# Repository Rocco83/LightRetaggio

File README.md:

# LightRetaggio

KiCad project for the LightRetaggioSchema board (LightController breakout), migrated from the original Eagle design.

## Repository layout

- `kicad/` — the active KiCad project (KiCad 10.0)
  - `LightRetaggioSchema.kicad_pro` — project file, open this in KiCad
  - `LightRetaggioSchema.kicad_sch` — schematic
  - `LightRetaggioSchema.kicad_pcb` — PCB layout
  - `LightRetaggioSchema-eagle-import.kicad_sym` — symbol library generated by the Eagle import
  - `LightRetaggioSchema.pretty/` — footprint library extracted from the imported board, registered in `fp-lib-table`
  - `sym-lib-table`, `fp-lib-table` — project-local library tables (paths are relative, no extra setup needed)
- `LightRetaggioSchema.sch` / `.brd` / `.pro` — original Eagle source (kept for reference)
- `LightRetaggioSchema_2020-04-23.zip` — archived Eagle export
- `eagle.epf` — Eagle workspace file

## Requirements

- [KiCad 10.0](https://www.kicad.org/download/) or newer

## Setup / build instructions

1. Install KiCad 10.0+.
2. Clone this repository:
   ```
   git clone https://github.com/Rocco83/LightRetaggio.git
   cd LightRetaggio
   ```
3. Open `kicad/LightRetaggioSchema.kicad_pro` in KiCad. The symbol and footprint libraries are referenced with relative paths in `sym-lib-table` / `fp-lib-table`, so no library setup is required beyond opening the project.
4. To edit: open the schematic (Eeschema) or PCB (Pcbnew) from the KiCad project manager.
5. To regenerate manufacturing outputs:
   - Gerbers/drill: Pcbnew → File → Fabrication Outputs → Gerbers / Drill Files
   - BOM: Eeschema → Tools → Generate Bill of Materials
   - Pick-and-place: Pcbnew → File → Fabrication Outputs → Component Placement Files

## Notes on the migration

The board was imported from the original Eagle source (rev V1.2, 2021-04-19) using KiCad's combined Eagle project importer. The importer generates a symbol library but no footprint library, so the footprints embedded in the imported board were extracted into `kicad/LightRetaggioSchema.pretty/` and registered under the `LightRetaggioSchema` nickname.

Verified clean after migration:
- **DRC**: 0 unconnected items, 0 footprint errors (remaining violations are cosmetic silkscreen/text sizing rules KiCad enforces more strictly than Eagle did)
- **ERC**: remaining violations are expected (unused switch pins, NC optocoupler pins, and a VCC/GND dual-net-naming convention already approved in the original Eagle file)

The original Eagle files (`.sch`, `.brd`, `.pro`) are kept at the repository root for reference/history.

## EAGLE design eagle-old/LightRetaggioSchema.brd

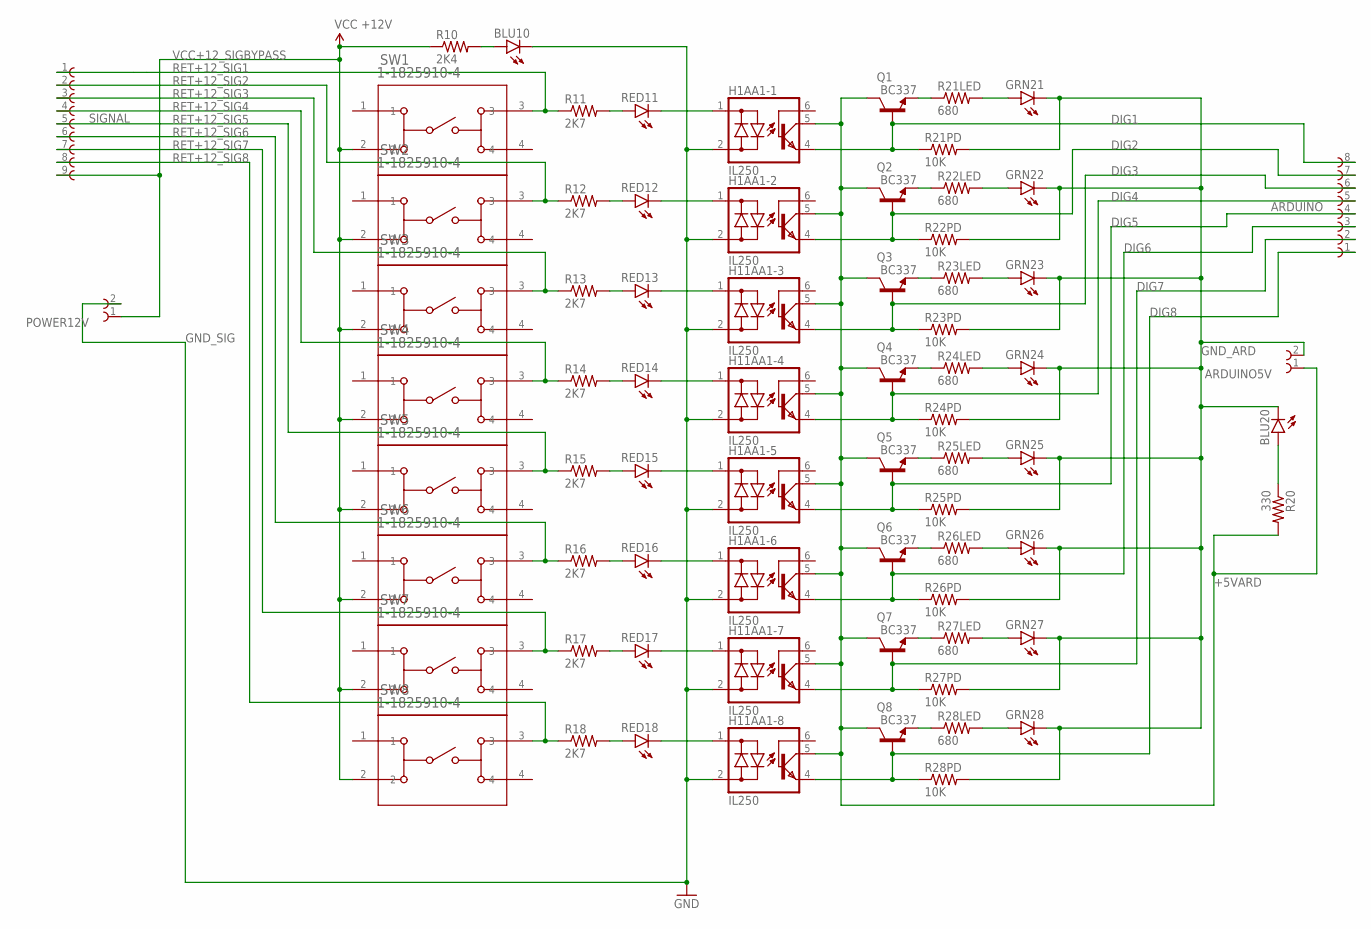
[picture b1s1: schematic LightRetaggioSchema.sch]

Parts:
ARDUINO: 691311500108
ARDUINO5V: 691311500102; MPN 691311500102
BLU10, BLU20: LED5MM; MPN FSM8JH
GRN21, GRN22, GRN23, GRN24, GRN25, GRN26, GRN27, GRN28: LED5MM; MPN FSM8JH
H1AA1-1, H1AA1-2, H1AA1-5, H1AA1-6, H11AA1-3, H11AA1-4, H11AA1-7, H11AA1-8: IL250; DIL06
POWER12V: 691311500102; MPN 691311500102
Q1, Q2, Q3, Q4, Q5, Q6, Q7, Q8: BC337; TO-92
R10: 2K4; AXIAL-0.4
R11, R12, R13, R14, R15, R16, R17, R18: 2K7; AXIAL-0.4
R20: 330; AXIAL-0.4
R21LED, R22LED, R23LED, R24LED, R25LED, R26LED, R27LED, R28LED: 680; AXIAL-0.4
R21PD, R22PD, R23PD, R24PD, R25PD, R26PD, R27PD, R28PD: 10K; AXIAL-0.4
RED11, RED12, RED13, RED14, RED15, RED16, RED17, RED18: LED5MM; MPN FSM8JH
SIGNAL: 691311500109
SW1, SW2, SW3, SW4, SW5, SW6, SW7, SW8: 1-1825910-4; SW4_1825910-D

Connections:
+5VARD: ARDUINO5V.1, H1AA1-1.5 (C), H1AA1-2.5 (C), H1AA1-5.5 (C), H1AA1-6.5 (C), H11AA1-3.5 (C), H11AA1-4.5 (C), H11AA1-7.5 (C), H11AA1-8.5 (C), Q1.1 (C), Q2.1 (C), Q3.1 (C), Q4.1 (C), Q5.1 (C), Q6.1 (C), Q7.1 (C), Q8.1 (C), R20.P$2 (2)
DIG1: ARDUINO.8, H1AA1-1.4 (E), Q1.2 (B), R21PD.P$1 (1)
DIG2: ARDUINO.7, H1AA1-2.4 (E), Q2.2 (B), R22PD.P$1 (1)
DIG3: ARDUINO.6, H11AA1-3.4 (E), Q3.2 (B), R23PD.P$1 (1)
DIG4: ARDUINO.5, H11AA1-4.4 (E), Q4.2 (B), R24PD.P$1 (1)
DIG5: ARDUINO.4, H1AA1-5.4 (E), Q5.2 (B), R25PD.P$1 (1)
DIG6: ARDUINO.3, H1AA1-6.4 (E), Q6.2 (B), R26PD.P$1 (1)
DIG7: ARDUINO.2, H11AA1-7.4 (E), Q7.2 (B), R27PD.P$1 (1)
DIG8: ARDUINO.1, H11AA1-8.4 (E), Q8.2 (B), R28PD.P$1 (1)
GND_ARD: ARDUINO5V.2, BLU20.K (C), GRN21.K (C), GRN22.K (C), GRN23.K (C), GRN24.K (C), GRN25.K (C), GRN26.K (C), GRN27.K (C), GRN28.K (C), R21PD.P$2 (2), R22PD.P$2 (2), R23PD.P$2 (2), R24PD.P$2 (2), R25PD.P$2 (2), R26PD.P$2 (2), R27PD.P$2 (2), R28PD.P$2 (2)
GND_SIG: BLU10.K (C), H1AA1-1.2 (AC2), H1AA1-2.2 (AC2), H1AA1-5.2 (AC2), H1AA1-6.2 (AC2), H11AA1-3.2 (AC2), H11AA1-4.2 (AC2), H11AA1-7.2 (AC2), H11AA1-8.2 (AC2), POWER12V.2
unnamed: BLU10.A, R10.P$2 (2)
unnamed: BLU20.A, R20.P$1 (1)
unnamed: H11AA1-8.1 (AC1), RED18.K (C)
unnamed: H11AA1-7.1 (AC1), RED17.K (C)
unnamed: H1AA1-6.1 (AC1), RED16.K (C)
unnamed: H1AA1-5.1 (AC1), RED15.K (C)
unnamed: Q1.3 (E), R21LED.P$1 (1)
unnamed: GRN21.A, R21LED.P$2 (2)
unnamed: H11AA1-4.1 (AC1), RED14.K (C)
unnamed: Q2.3 (E), R22LED.P$1 (1)
unnamed: GRN22.A, R22LED.P$2 (2)
unnamed: Q3.3 (E), R23LED.P$1 (1)
unnamed: GRN23.A, R23LED.P$2 (2)
unnamed: Q4.3 (E), R24LED.P$1 (1)
unnamed: GRN24.A, R24LED.P$2 (2)
unnamed: R13.P$2 (2), RED13.A
unnamed: H11AA1-3.1 (AC1), RED13.K (C)
unnamed: R14.P$2 (2), RED14.A
unnamed: R12.P$2 (2), RED12.A
unnamed: R11.P$2 (2), RED11.A
unnamed: R17.P$2 (2), RED17.A
unnamed: R18.P$2 (2), RED18.A
unnamed: R16.P$2 (2), RED16.A
unnamed: R15.P$2 (2), RED15.A
unnamed: Q5.3 (E), R25LED.P$1 (1)
unnamed: GRN25.A, R25LED.P$2 (2)
unnamed: Q6.3 (E), R26LED.P$1 (1)
unnamed: GRN26.A, R26LED.P$2 (2)
unnamed: Q7.3 (E), R27LED.P$1 (1)
unnamed: GRN27.A, R27LED.P$2 (2)
unnamed: Q8.3 (E), R28LED.P$1 (1)
unnamed: GRN28.A, R28LED.P$2 (2)
unnamed: H1AA1-2.1 (AC1), RED12.K (C)
unnamed: H1AA1-1.1 (AC1), RED11.K (C)
RET+12_SIG1: R11.P$1 (1), SIGNAL.1, SW1.3
RET+12_SIG2: R12.P$1 (1), SIGNAL.2, SW2.3
RET+12_SIG3: R13.P$1 (1), SIGNAL.3, SW3.3
RET+12_SIG4: R14.P$1 (1), SIGNAL.4, SW4.3
RET+12_SIG5: R15.P$1 (1), SIGNAL.5, SW5.3
RET+12_SIG6: R16.P$1 (1), SIGNAL.6, SW6.3
RET+12_SIG7: R17.P$1 (1), SIGNAL.7, SW7.3
RET+12_SIG8: R18.P$1 (1), SIGNAL.8, SW8.3
VCC+12_SIGBYPASS: POWER12V.1, R10.P$1 (1), SIGNAL.9, SW1.2, SW2.2, SW3.2, SW4.2, SW5.2, SW6.2, SW7.2, SW8.2

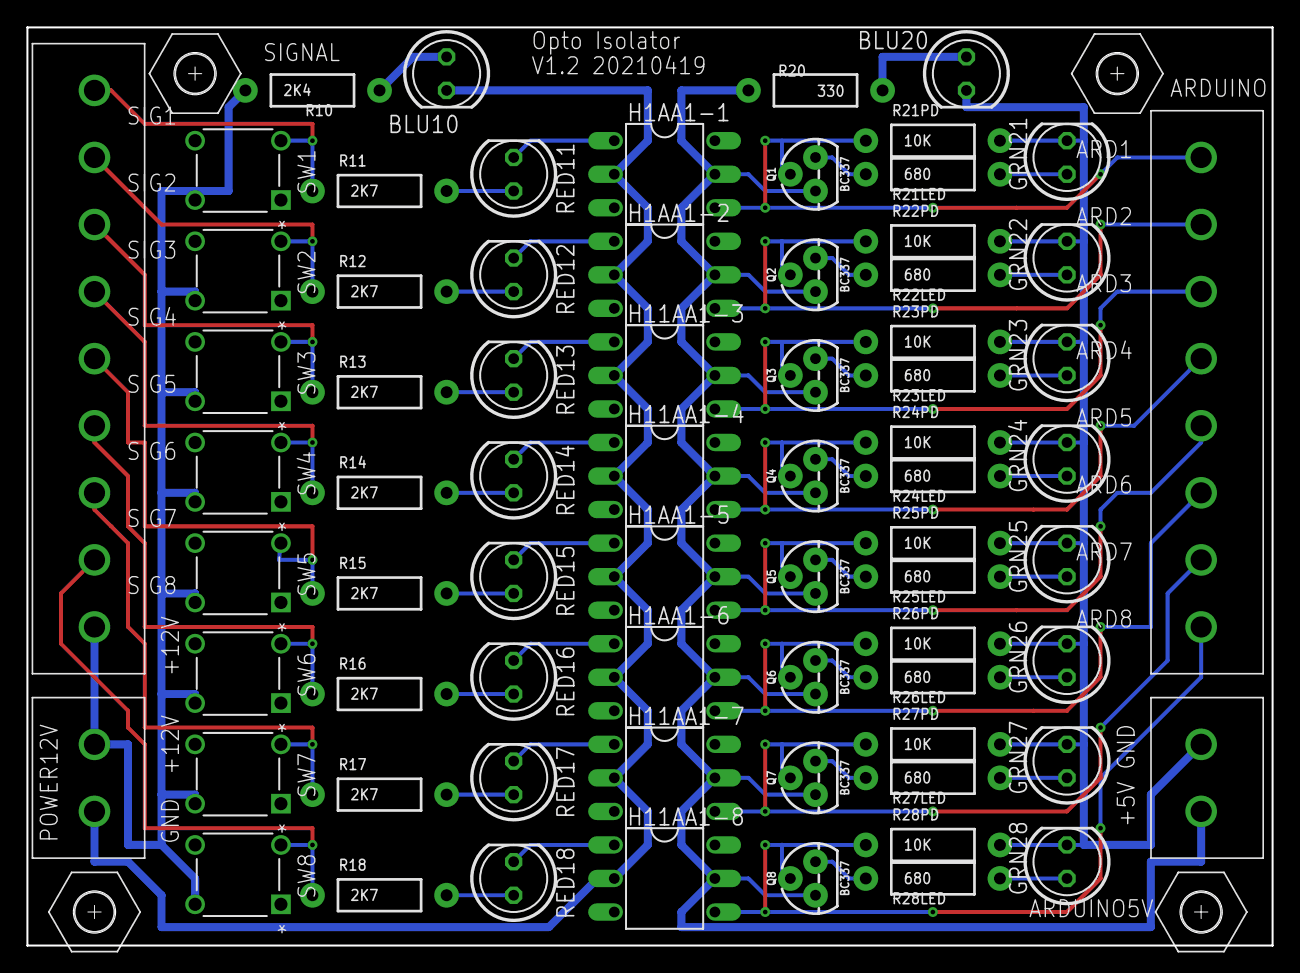
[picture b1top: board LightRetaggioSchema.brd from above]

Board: 2 copper layers, 94.3 x 69.5 mm, 76 parts (0 on the bottom side), 54 nets.

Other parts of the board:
U$1, U$2, U$3, U$5: M3.0_SW6.0

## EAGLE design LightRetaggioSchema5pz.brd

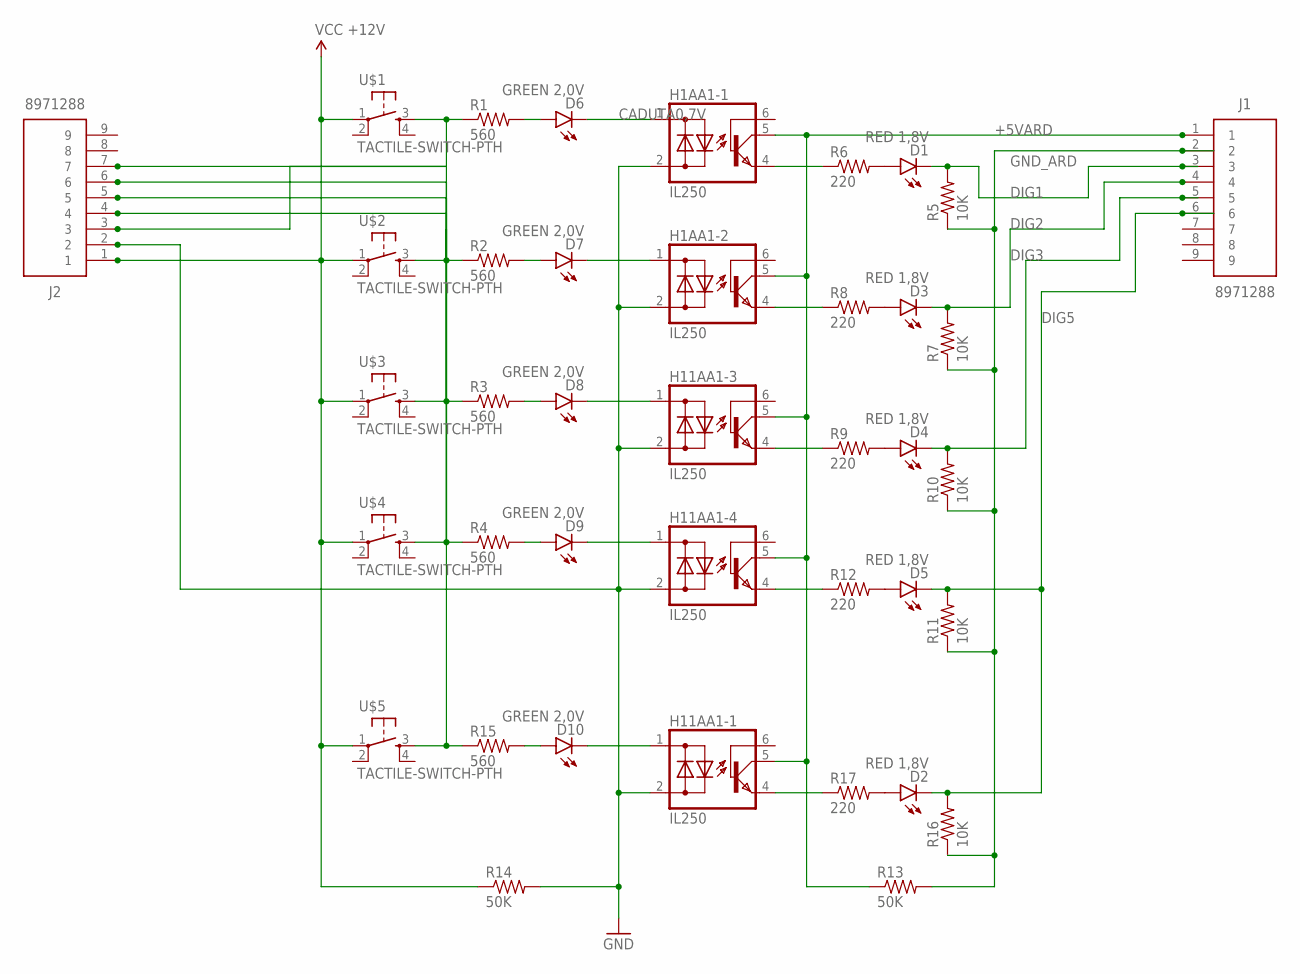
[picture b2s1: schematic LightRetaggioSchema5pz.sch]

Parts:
D1, D2, D3, D4, D5: RED 1,8V; LED-1206
D6, D7, D8, D9, D10: GREEN 2,0V; LED-1206
H1AA1-1, H1AA1-2, H11AA1-1, H11AA1-3, H11AA1-4: IL250; DIL06
J1, J2: 8971288; SHDR9W100P0X508_1X9_4690X1210X
R1, R2, R3, R4, R15: 560; AXIAL-0.4
R5, R7, R10, R11, R16: 10K; AXIAL-0.4
R6, R8, R9, R12, R17: 220; AXIAL-0.4
R13, R14: 50K; AXIAL-0.4
U$1, U$2, U$3, U$4, U$5: TACTILE-SWITCH-PTH; TAC-SWITCH-PTH

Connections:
+5VARD: H1AA1-1.5 (C), H1AA1-2.5 (C), H11AA1-1.5 (C), H11AA1-3.5 (C), H11AA1-4.5 (C), J1.1, R13.P$1 (1)
CADUTA0,7V: D6.C, H1AA1-1.1 (AC1)
DIG1: D1.C, J1.3, R5.P$2 (2)
DIG2: D3.C, J1.4, R7.P$2 (2)
DIG3: D4.C, J1.5, R10.P$2 (2)
DIG5: D2.C, D5.C, J1.6, R11.P$2 (2), R16.P$2 (2)
GND: H1AA1-1.2 (AC2), H1AA1-2.2 (AC2), H11AA1-1.2 (AC2), H11AA1-3.2 (AC2), H11AA1-4.2 (AC2), J2.2, R14.P$2 (2)
GND_ARD: J1.2, R5.P$1 (1), R7.P$1 (1), R10.P$1 (1), R11.P$1 (1), R13.P$2 (2), R16.P$1 (1)
unnamed: J2.4, J2.5, R3.P$1 (1), U$3.3
unnamed: R2.P$1 (1), U$2.3
unnamed: J2.6, R4.P$1 (1), U$4.3
unnamed: D9.C, H11AA1-4.1 (AC1)
unnamed: D8.C, H11AA1-3.1 (AC1)
unnamed: D7.C, H1AA1-2.1 (AC1)
unnamed: J2.3, R1.P$1 (1), U$1.3
unnamed: H1AA1-1.4 (E), R6.P$1 (1)
unnamed: D1.A, R6.P$2 (2)
unnamed: D4.A, R9.P$2 (2)
unnamed: D3.A, R8.P$2 (2)
unnamed: H1AA1-2.4 (E), R8.P$1 (1)
unnamed: D5.A, R12.P$2 (2)
unnamed: H11AA1-4.4 (E), R12.P$1 (1)
unnamed: D8.A, R3.P$2 (2)
unnamed: H11AA1-3.4 (E), R9.P$1 (1)
unnamed: D9.A, R4.P$2 (2)
unnamed: D7.A, R2.P$2 (2)
unnamed: D6.A, R1.P$2 (2)
unnamed: J2.7, R15.P$1 (1), U$5.3
unnamed: D10.C, H11AA1-1.1 (AC1)
unnamed: D2.A, R17.P$2 (2)
unnamed: H11AA1-1.4 (E), R17.P$1 (1)
unnamed: D10.A, R15.P$2 (2)
VCC: J2.1, R14.P$1 (1), U$1.1, U$2.1, U$3.1, U$4.1, U$5.1

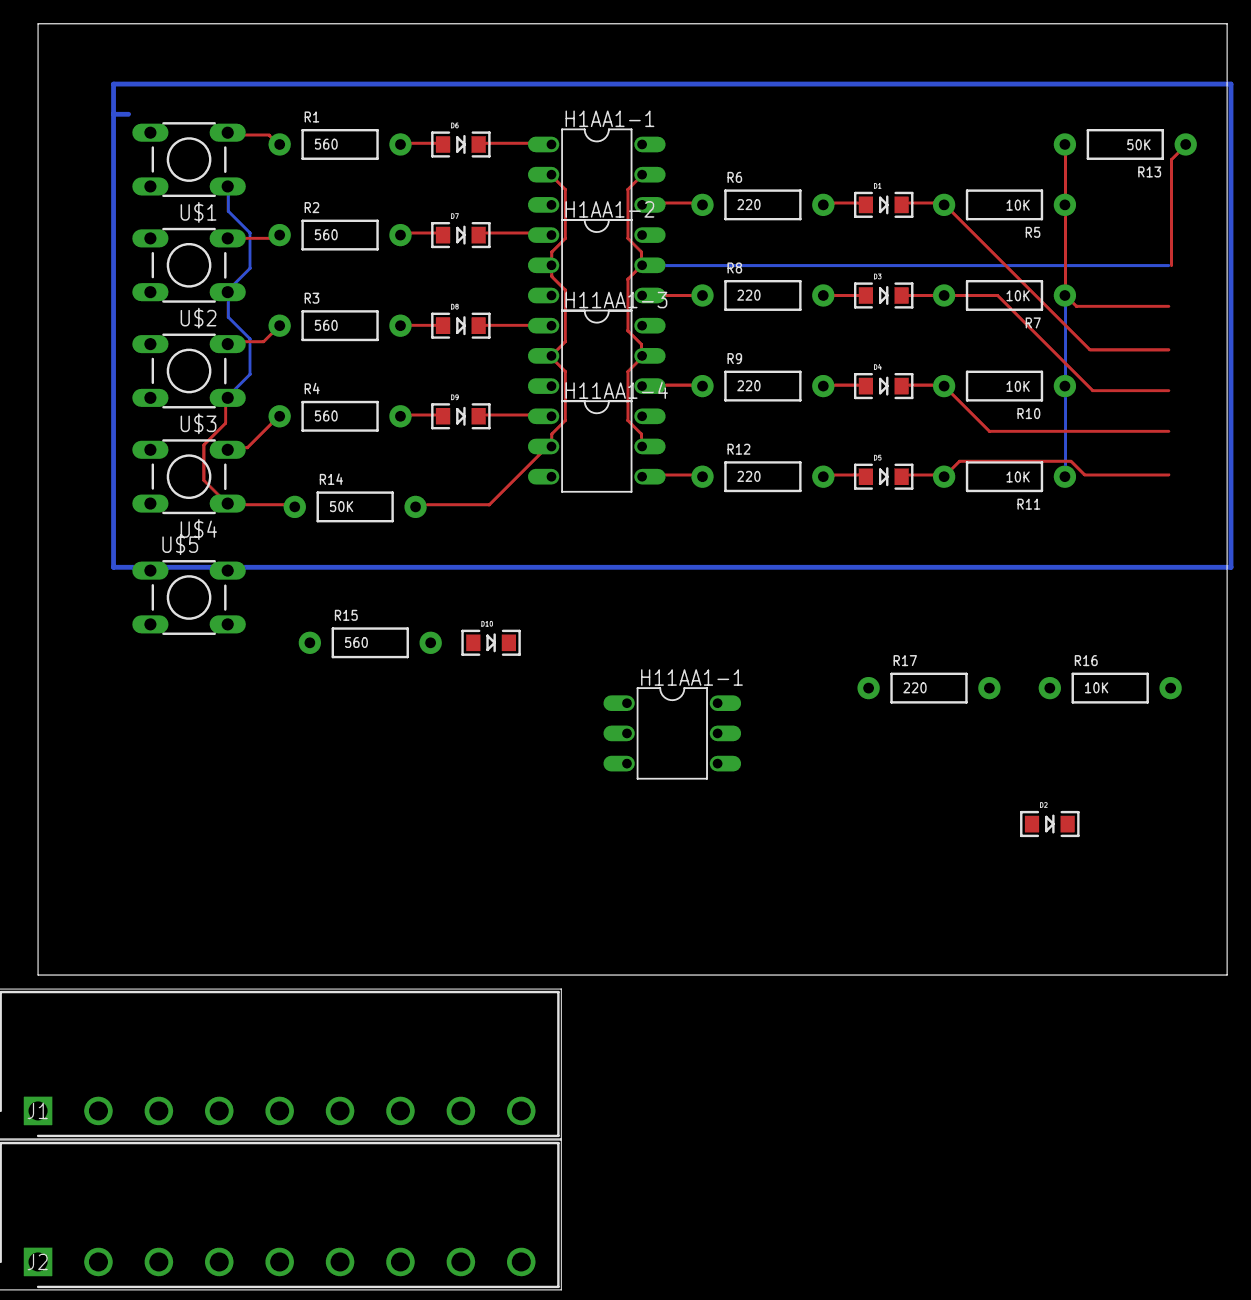
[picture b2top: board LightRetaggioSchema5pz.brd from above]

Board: 2 copper layers, 100.0 x 80.0 mm, 39 parts (0 on the bottom side), 33 nets.

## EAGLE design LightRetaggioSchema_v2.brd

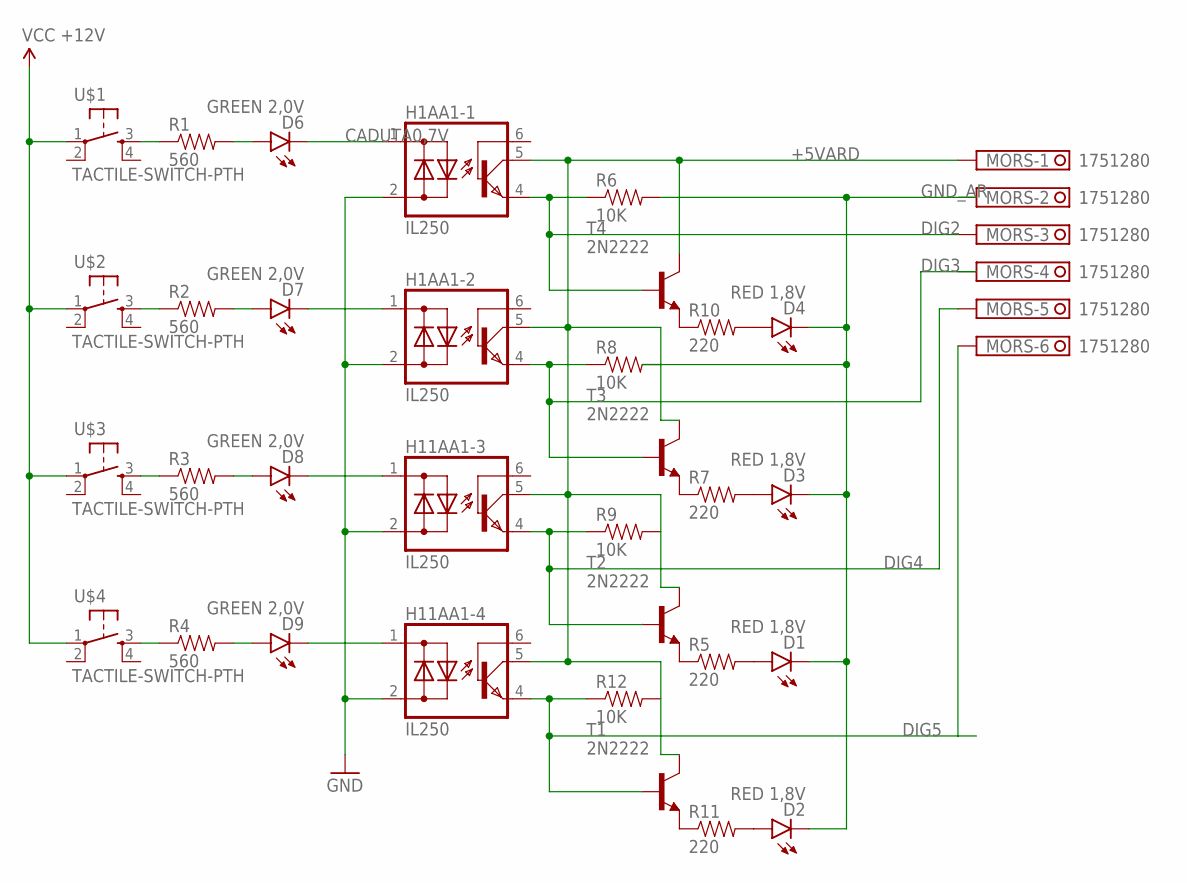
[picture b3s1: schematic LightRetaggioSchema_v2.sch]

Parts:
D1, D2, D3, D4: RED 1,8V; LED-1206
D6, D7, D8, D9: GREEN 2,0V; LED-1206
H1AA1-1, H1AA1-2, H11AA1-3, H11AA1-4: IL250; DIL06
MORS: 1751280
R1, R2, R3, R4: 560; AXIAL-0.4
R5, R7, R10, R11: 220; AXIAL-0.4
R6, R8, R9, R12: 10K; AXIAL-0.4
T1, T2, T3, T4: 2N2222; TO18
U$1, U$2, U$3, U$4: TACTILE-SWITCH-PTH; TAC-SWITCH-PTH

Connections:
+5VARD: H1AA1-1.5 (C), H1AA1-2.5 (C), H11AA1-3.5 (C), H11AA1-4.5 (C), MORS.1, T1.3 (C), T2.3 (C), T3.3 (C), T4.3 (C)
CADUTA0,7V: D6.C, H1AA1-1.1 (AC1)
DIG2: H1AA1-1.4 (E), MORS.3, R6.P$1 (1), T4.2 (B)
DIG3: H1AA1-2.4 (E), R8.P$1 (1), T3.2 (B)
DIG4: H11AA1-3.4 (E), MORS.5, R9.P$1 (1), T2.2 (B)
DIG5: H11AA1-4.4 (E), MORS.6, R12.P$1 (1), T1.2 (B)
GND: H1AA1-1.2 (AC2), H1AA1-2.2 (AC2), H11AA1-3.2 (AC2), H11AA1-4.2 (AC2)
GND_AR: D1.C, D2.C, D3.C, D4.C, R6.P$2 (2)
unnamed: R3.P$1 (1), U$3.3
unnamed: R2.P$1 (1), U$2.3
unnamed: R4.P$1 (1), U$4.3
unnamed: D9.C, H11AA1-4.1 (AC1)
unnamed: D8.C, H11AA1-3.1 (AC1)
unnamed: D7.C, H1AA1-2.1 (AC1)
unnamed: R1.P$1 (1), U$1.3
unnamed: R5.P$1 (1), T2.1 (E)
unnamed: D2.A, R11.P$2 (2)
unnamed: D8.A, R3.P$2 (2)
unnamed: D9.A, R4.P$2 (2)
unnamed: D7.A, R2.P$2 (2)
unnamed: D6.A, R1.P$2 (2)
unnamed: R11.P$1 (1), T1.1 (E)
unnamed: D1.A, R5.P$2 (2)
unnamed: R7.P$1 (1), T3.1 (E)
unnamed: D3.A, R7.P$2 (2)
unnamed: R10.P$1 (1), T4.1 (E)
unnamed: D4.A, R10.P$2 (2)
VCC: U$1.1, U$2.1, U$3.1, U$4.1

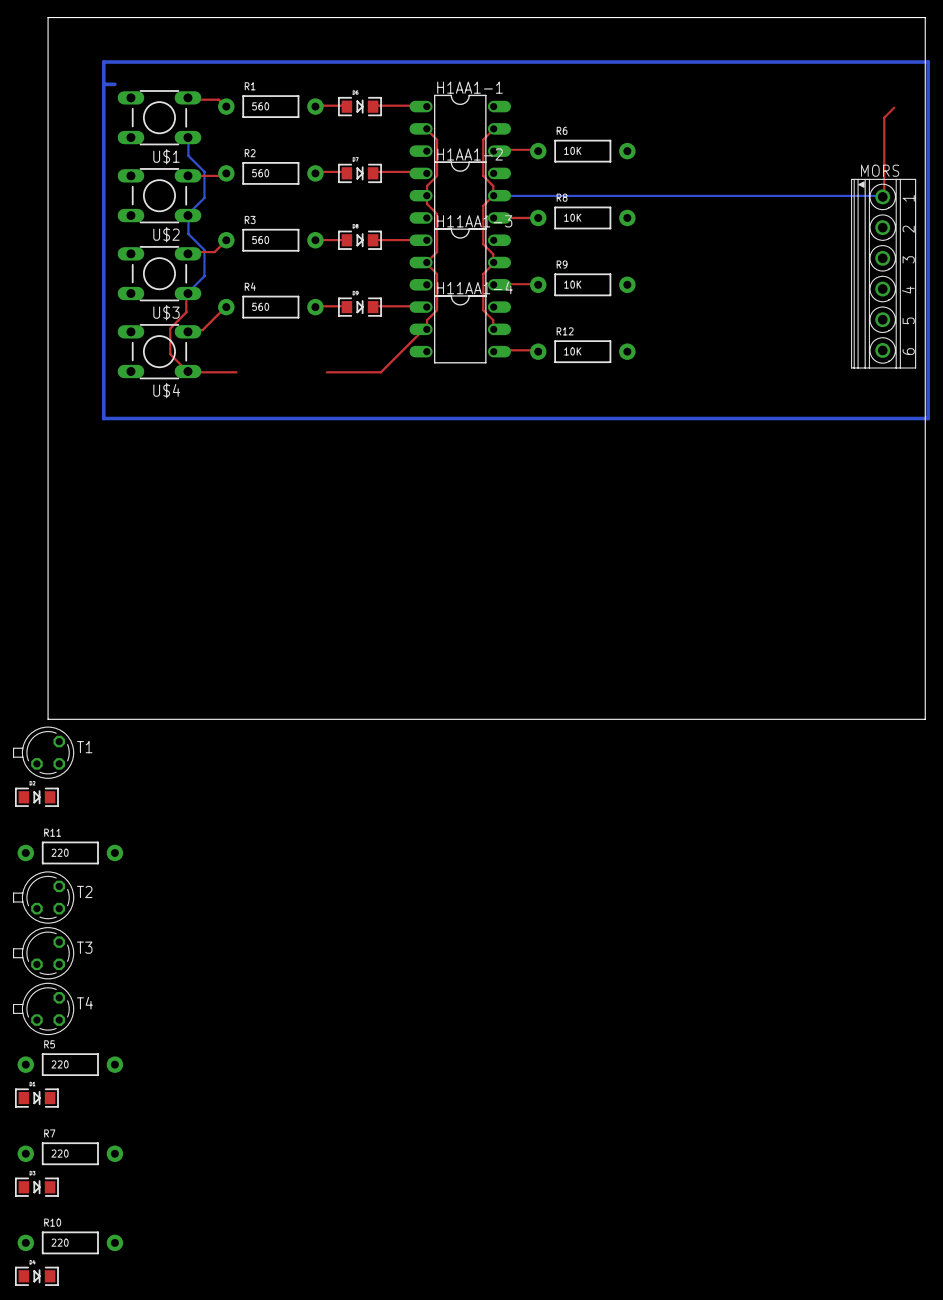
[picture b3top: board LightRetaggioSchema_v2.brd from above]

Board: 2 copper layers, 100.0 x 80.0 mm, 33 parts (0 on the bottom side), 28 nets.

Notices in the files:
parts and their libraries:
SparkFun-LED: Licensing: Creative Commons ShareAlike 4.0 International - https://creativecommons.org/licenses/by-sa/4.0
Wurth_Elektronik_Electromechanic_Termina: Copyright: Würth Elektronik
COPYRIGHT: Copyright (C) 2016 Accelerated Designs. All rights reserved
